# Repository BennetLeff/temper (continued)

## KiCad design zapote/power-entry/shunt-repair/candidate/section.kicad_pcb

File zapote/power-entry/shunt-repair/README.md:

# Shunt repair and electrical-model completion

Execution contract, 2026-09-16, starting at b7af4c912.

The approved work is shunt/copper thermal modeling, remaining current paths,
actual switching loops and startup/fault/loss-of-bias behavior. First resolve
an invalid model input: the authored WSL2726R0100FEA at 10 mΩ with two pads
is outside Vishay's published WSL2726 range and four-terminal package.
Source/native agreement did not detect this part-definition defect.

1. Retain exact manufacturer evidence and choose an available 10 mΩ shunt,
   preserving the controller's sense scaling. Bind MPN, resistance, package,
   land pattern and conditional power rating in Rust. Preserve the historical
   board as a failing regression; never rewrite historical source receipts.
2. Update authored source, compile with Atopile, refresh the saved working
   PCB/schematic and native receipts, and run construction/physical checks.
3. Model actual new shunt/copper geometry with explicit cooling and material
   uncertainty. Require energy balance, mesh convergence and sensitivities;
   a catalog wattage is not a temperature prediction or assembly qualification.
4. Resolve switching-loop and controller protection paths from source and
   manufacturer behavior. Keep missing external supervision and response-time
   bounds visible. Do not invent a safety deadline.
5. Run common harness and regression mutations; retain raw inputs/results and
   record remaining model or assembly limitations before committing/pushing.

Evidence belongs here and in a dated common-suite run. Historical GBU/GBJ
thermal results remain valid only for their original saved inputs. A changed
board is not allowed to inherit their acceptance by editing a hash.

No fabrication, purchase or powered measurement is part of this execution.

## Implemented repair

The working authoring source now uses GBJ2510-F and Stackpole
HCSM2818FT10L0 (10 mΩ, ±1%, two terminals). The historical GBU and GBJ
fixtures remain unchanged. Their unsupported WSL2726 shunt definition is now
an explicit `ERC.PFC.SHUNT_PART` failure, including in regression tests.

The replacement was compiled through Atopile, projected into native KiCad,
then applied to the routed GBJ candidate with its physical UUIDs preserved.
The land pattern uses two 3.5 × 5.3 mm rectangles, a 0.6 mm gap and a
7.15 × 4.95 mm body. The official KiCad Library Tools generator and parameters
are retained. Manufacturer documents, exact identities and source hashes are
in [sources/manifest.json](sources/manifest.json).

U12's left power trace is 5.3 mm wide and ends at (75.3, 132) mm, retaining
the sense-wire junction. A 6 mm trace ending there would short the new opposite
pad; shortening it first to 74.7 mm avoided that short but left a width-only
contact that the current graph could not resolve. The final edit repairs both
conditions. Its round cap stops at x = 77.95 mm; the opposite pad begins at
78.30 mm. Native DRC checks the resulting 0.35 mm clearance. The narrower trace
is subject to the same current screen as every other trace; no waiver was added.

Authoritative candidate: [candidate/section.kicad_pcb](candidate/section.kicad_pcb).
Use [units.json](units.json) to run the seven-unit suite with this working
candidate. The default maintained registry intentionally retains its historical
board; it does not silently acquire this candidate or its thermal evidence.

## What the thermal experiment establishes

[thermal-04/report.json](thermal-04/report.json) contains 15 actual Gmsh/Elmer
solves: five boundary/material/heat-split cases on three successively finer
meshes. Native front pads, local track rectangles and round ends are modeled
as separate copper domains. Independent Rust checks integrate mesh volumes,
check pad source volumes and cut areas, reject a bridged gap or internal clamp,
and require two connected domains with cooling boundaries. Both the Gmsh and
converted Elmer meshes are checked.

The heat source is 2.28528 W: 15 A RMS through 10 mΩ, with +1% resistance and
+75 ppm/K evaluated at 100 °C. It is a conditional input, not a temperature-
iterated worst-case bound. Heat balance, solver convergence and mesh convergence
are checked from raw output. Uniformly raising cut temperatures by 20 K raises
the result by 20 K; reducing copper conductivity from 350 to 250 W/(m·K)
scales the rise by 1.4, providing independent linear-equation checks.

| Case, finest mesh | Peak modeled local copper |
|---|---:|
| 80 °C cuts, equal terminal heat | 122.68 °C |
| 80 °C cuts, all heat into terminal 1 | 162.74 °C |
| 80 °C cuts, all heat into terminal 2 | 165.37 °C |
| 100 °C cuts, equal terminal heat | 142.68 °C |
| 80 °C cuts, weaker copper conductivity | 139.76 °C |

These are **not predictions of resistor body temperature or evidence that the
real board overheats**. The model omits body/solder conduction, vias, back copper,
FR4, convection and copper Joule heat. Parallel heat paths may cool the actual
assembly; other losses may heat it. The imposed cut temperatures need a board/
assembly cooling model. The 5 W catalog rating requires specified copper and
surface temperature conditions, which this model does not establish.
`THERMAL.PFC.SHUNT_ASSEMBLY` therefore remains INDETERMINATE.

Replay binds the exact saved board, source-bound 15 A waveform, geometry, decks,
backend/module digests, meshes, raw logs and measurements. Edited summaries,
changed decks even with updated checksums, missing heat materials, incorrect
boundaries, nonconverged solves and unbalanced heat are regression failures.
The first empty-region mesher attempt and subsequent historical runs are kept
as development evidence; they cannot be substituted for this final run.

## Controller and switching-loop coverage

The common runner executes the source-bound UCC28180 threshold cases. UVLO,
standby, high OVP/reset, open current sense, soft current limit and peak current
limit distinguish guaranteed threshold crossings from tolerance bands.
The ICOMP table/prose unit conflict remains INDETERMINATE. No guaranteed
shutdown propagation time or gate-voltage behavior at zero bias is invented.
Controller inhibition does not disconnect mains or discharge the DC bus.

Named boost-commutation, gate-drive and on-state input loops are checked against
source pin identities and native conductor paths. Bridge polarity is resolved
from its exact MPN. Returned edge IDs are connectivity witnesses, not extracted
high-frequency current paths. Loop geometry and parasitic inductance remain
explicit mandatory INDETERMINATE checks; a whole-net bounding box cannot satisfy
them.

## Remaining physical obligations

1. Resolve shunt body/terminal thermal parameters and actual board cooling,
   including vias and back copper; then evaluate resistor surface temperature
   and transient/pulse capability under the operating envelope.
2. Extract high-frequency return paths and parasitics for the named loops.
3. Supply the external bias, permit/precharge, disconnect and discharge contracts;
   validate their startup and fault timing with the power stage.
4. Complete inductor, switch, diode, capacitor and remaining pad/via loss/rating
   corners before calling the power-entry assembly qualified.

The new checks make these omissions visible. Numerical PASS, source agreement
and native DRC PASS are each narrower than hardware qualification.

## Final validation, 2026-09-16

[Final receipt](evidence/final-validation.json) binds the board and source hashes.
The [seven-unit run](../../validation/runs/shunt-20260916-final-02/summary.json)
has zero native ERC/DRC/unconnected/parity findings and zero Rust failures.
Every overall unit verdict remains INDETERMINATE because physical/integration
obligations are not waived. The workspace tests report 473 passed, zero failed,
one ignored. Clippy reports only the 15 previously present warnings; import
boundaries and generated-artifact consistency checks pass.

The bridge evidence was regenerated from this exact candidate: 96 local solves
under [bridge-thermal-02](bridge-thermal-02/assessment.json), with nominal mesh
deltas 0.04383/0.02454 K and wider-domain delta 0.01685 K. No historical bridge
result was made current by changing its input hash. Required raw meshes, scalar
measurements, decks, logs and tool receipts are retained; gzip archives preserve
their original-byte hashes. Optional nodal restart fields are retained locally
at the location and digests recorded in `bridge-thermal-02/field-archive.json`;
they are not inputs to the acceptance replay.

`shunt-20260916-final` is a rejected attempt: archiving those optional restart
fields overlapped its input read, and the integrity guard refused the run.
`shunt-20260916-final-02` is the completed immutable-input rerun. Earlier failed
geometry, copper and model attempts are retained with their actual outcomes.

[Code-review receipt](../../../docs/reviews/shunt-20260916/run-20260916-shunt/review.json)
reports no actionable findings. Its coverage limitations are retained. No
hardware was powered, no purchase was placed and no fabrication order was made.

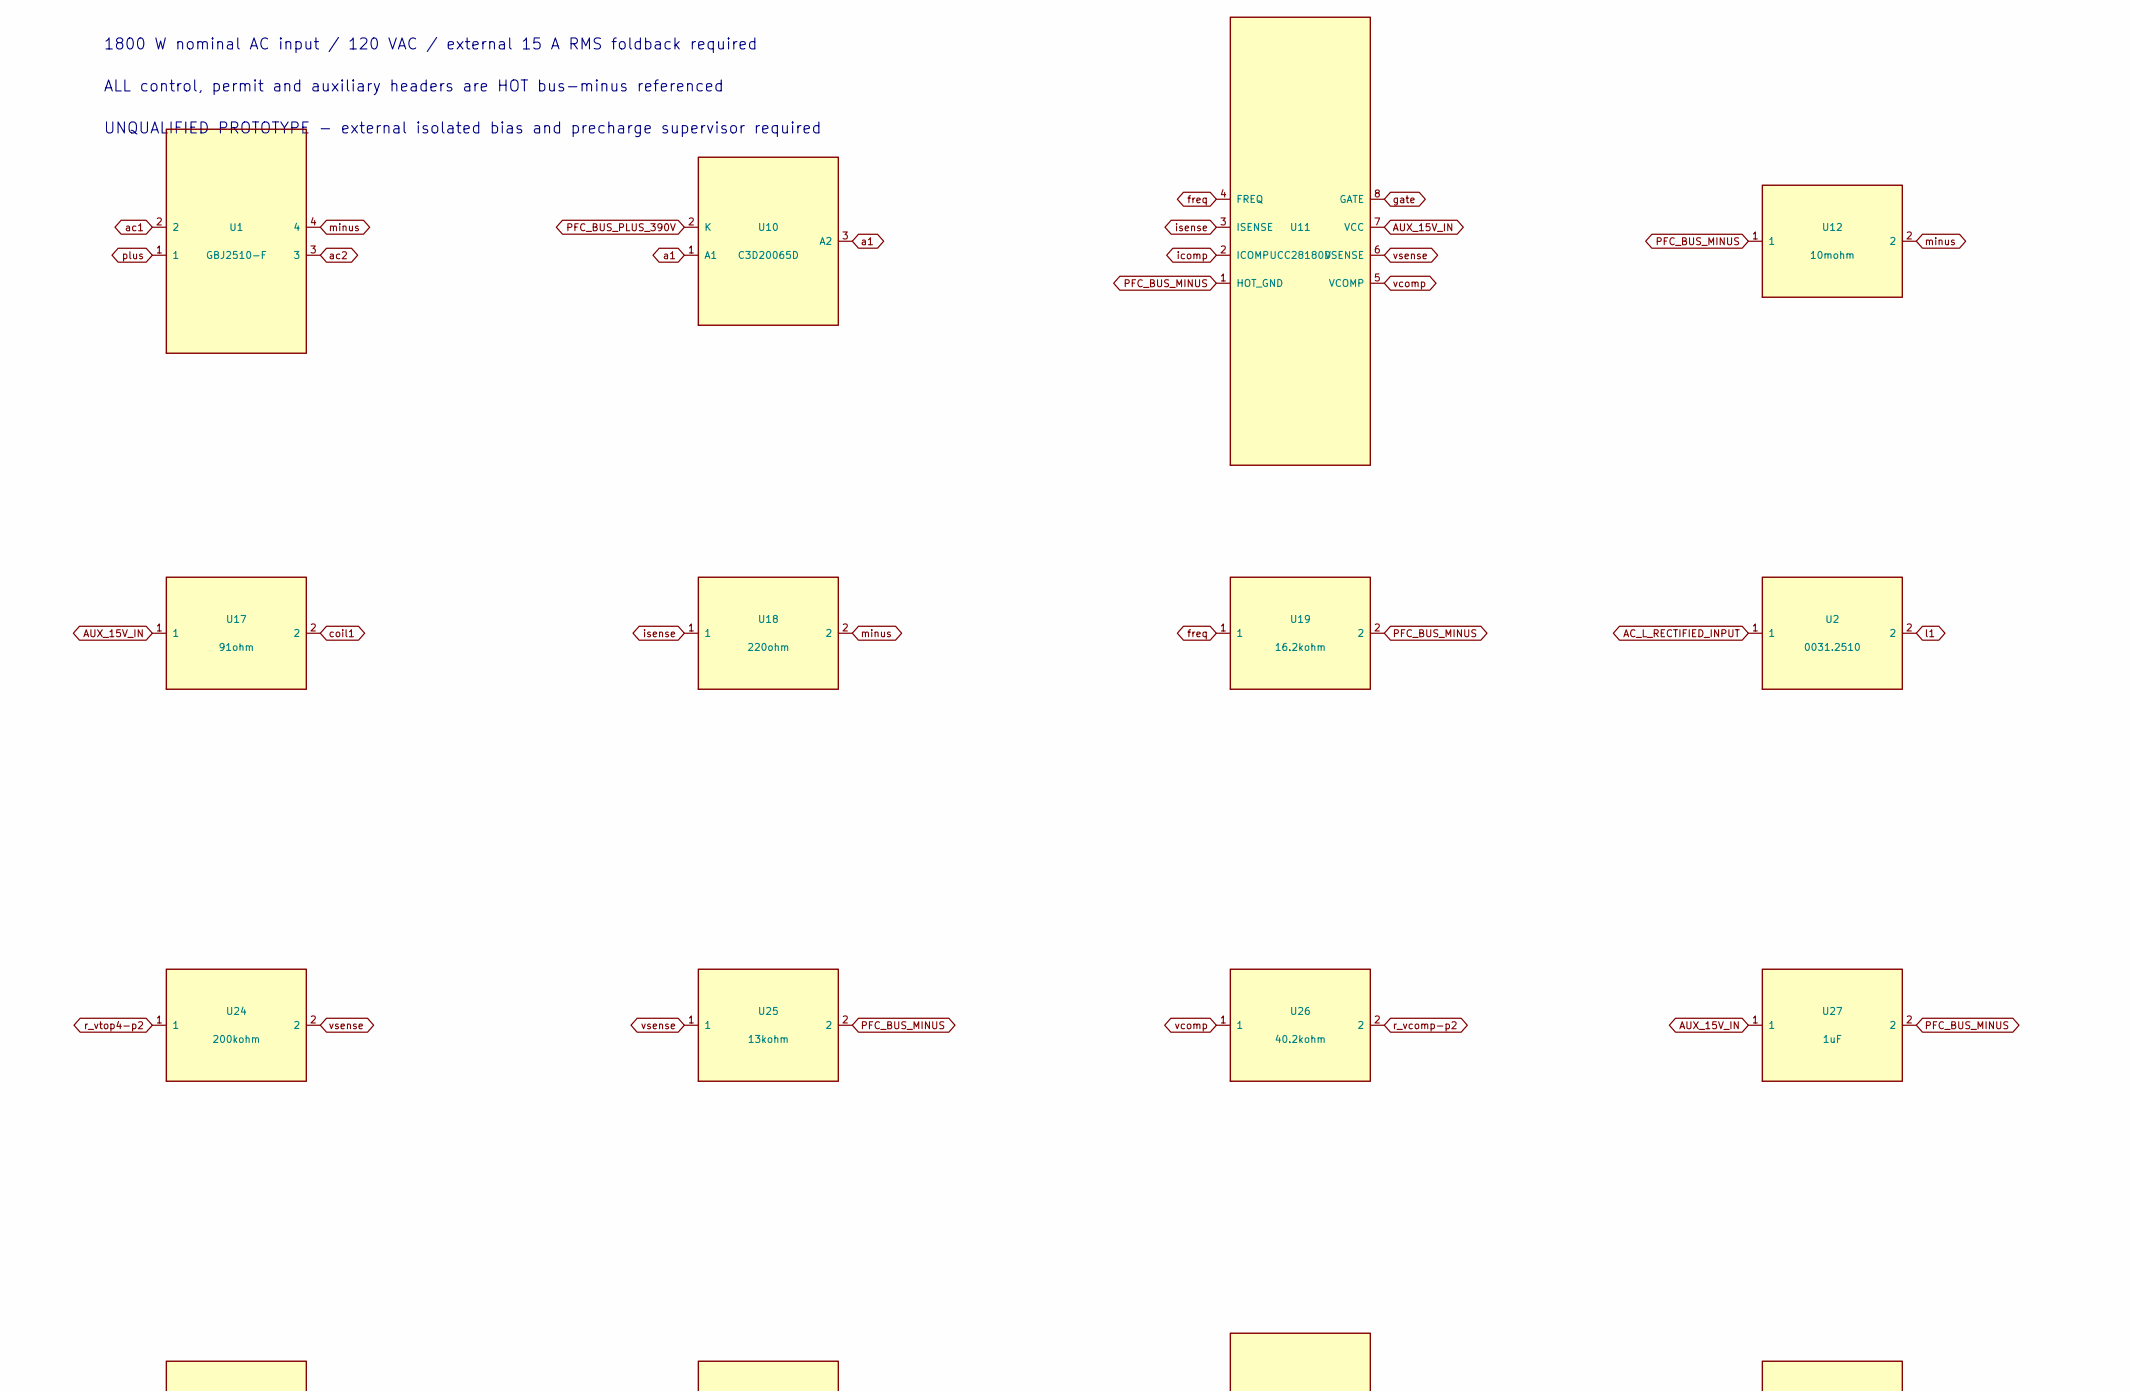
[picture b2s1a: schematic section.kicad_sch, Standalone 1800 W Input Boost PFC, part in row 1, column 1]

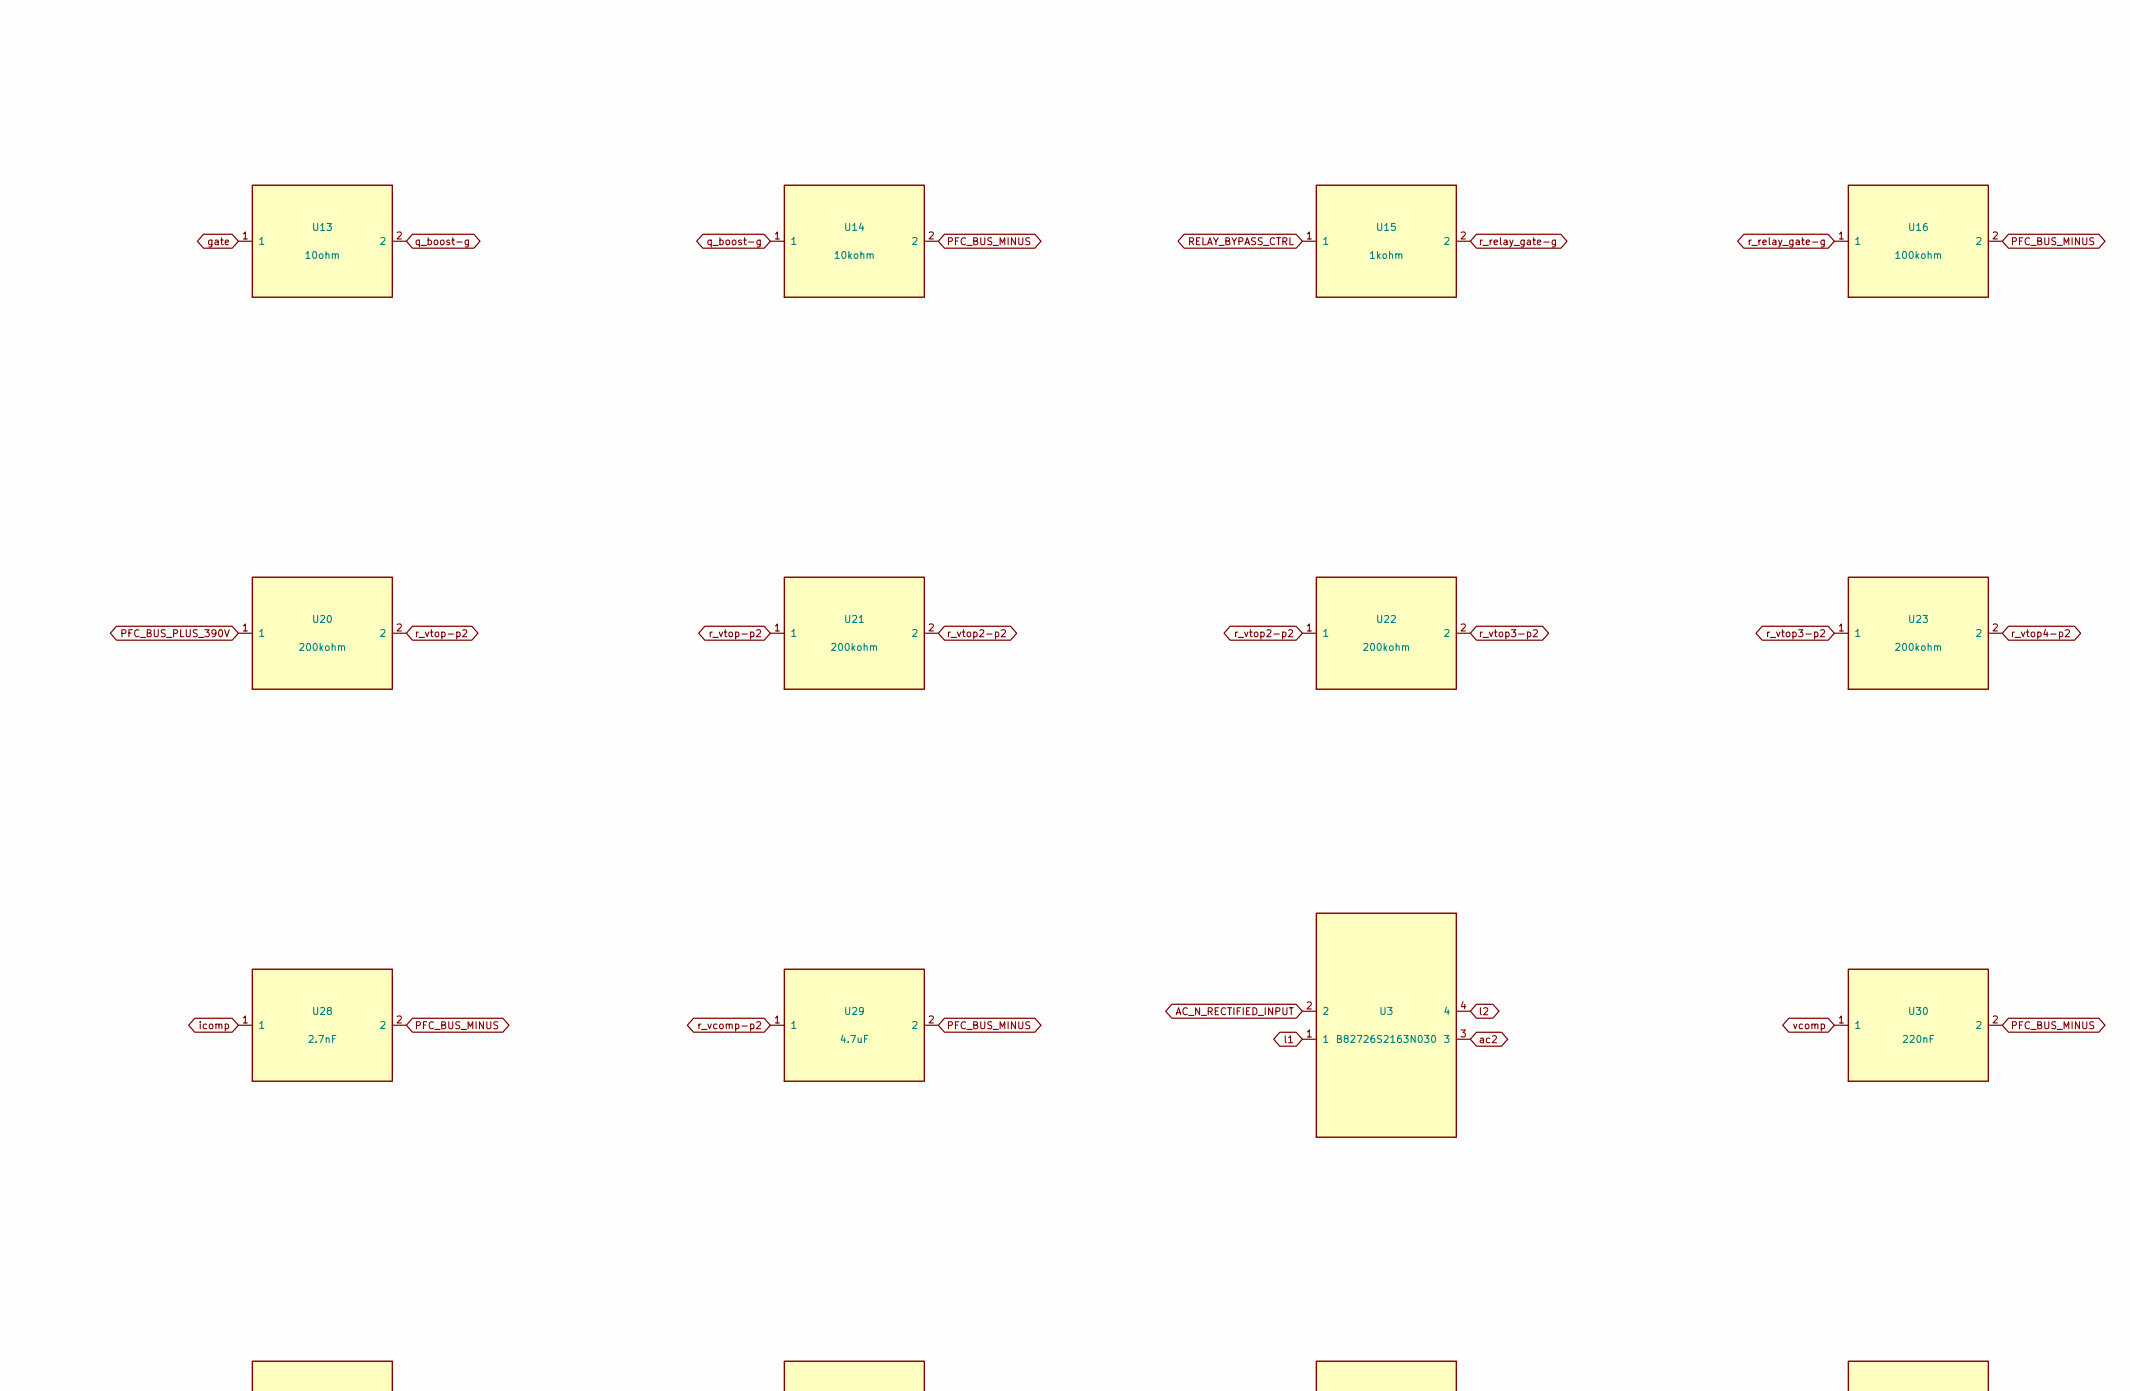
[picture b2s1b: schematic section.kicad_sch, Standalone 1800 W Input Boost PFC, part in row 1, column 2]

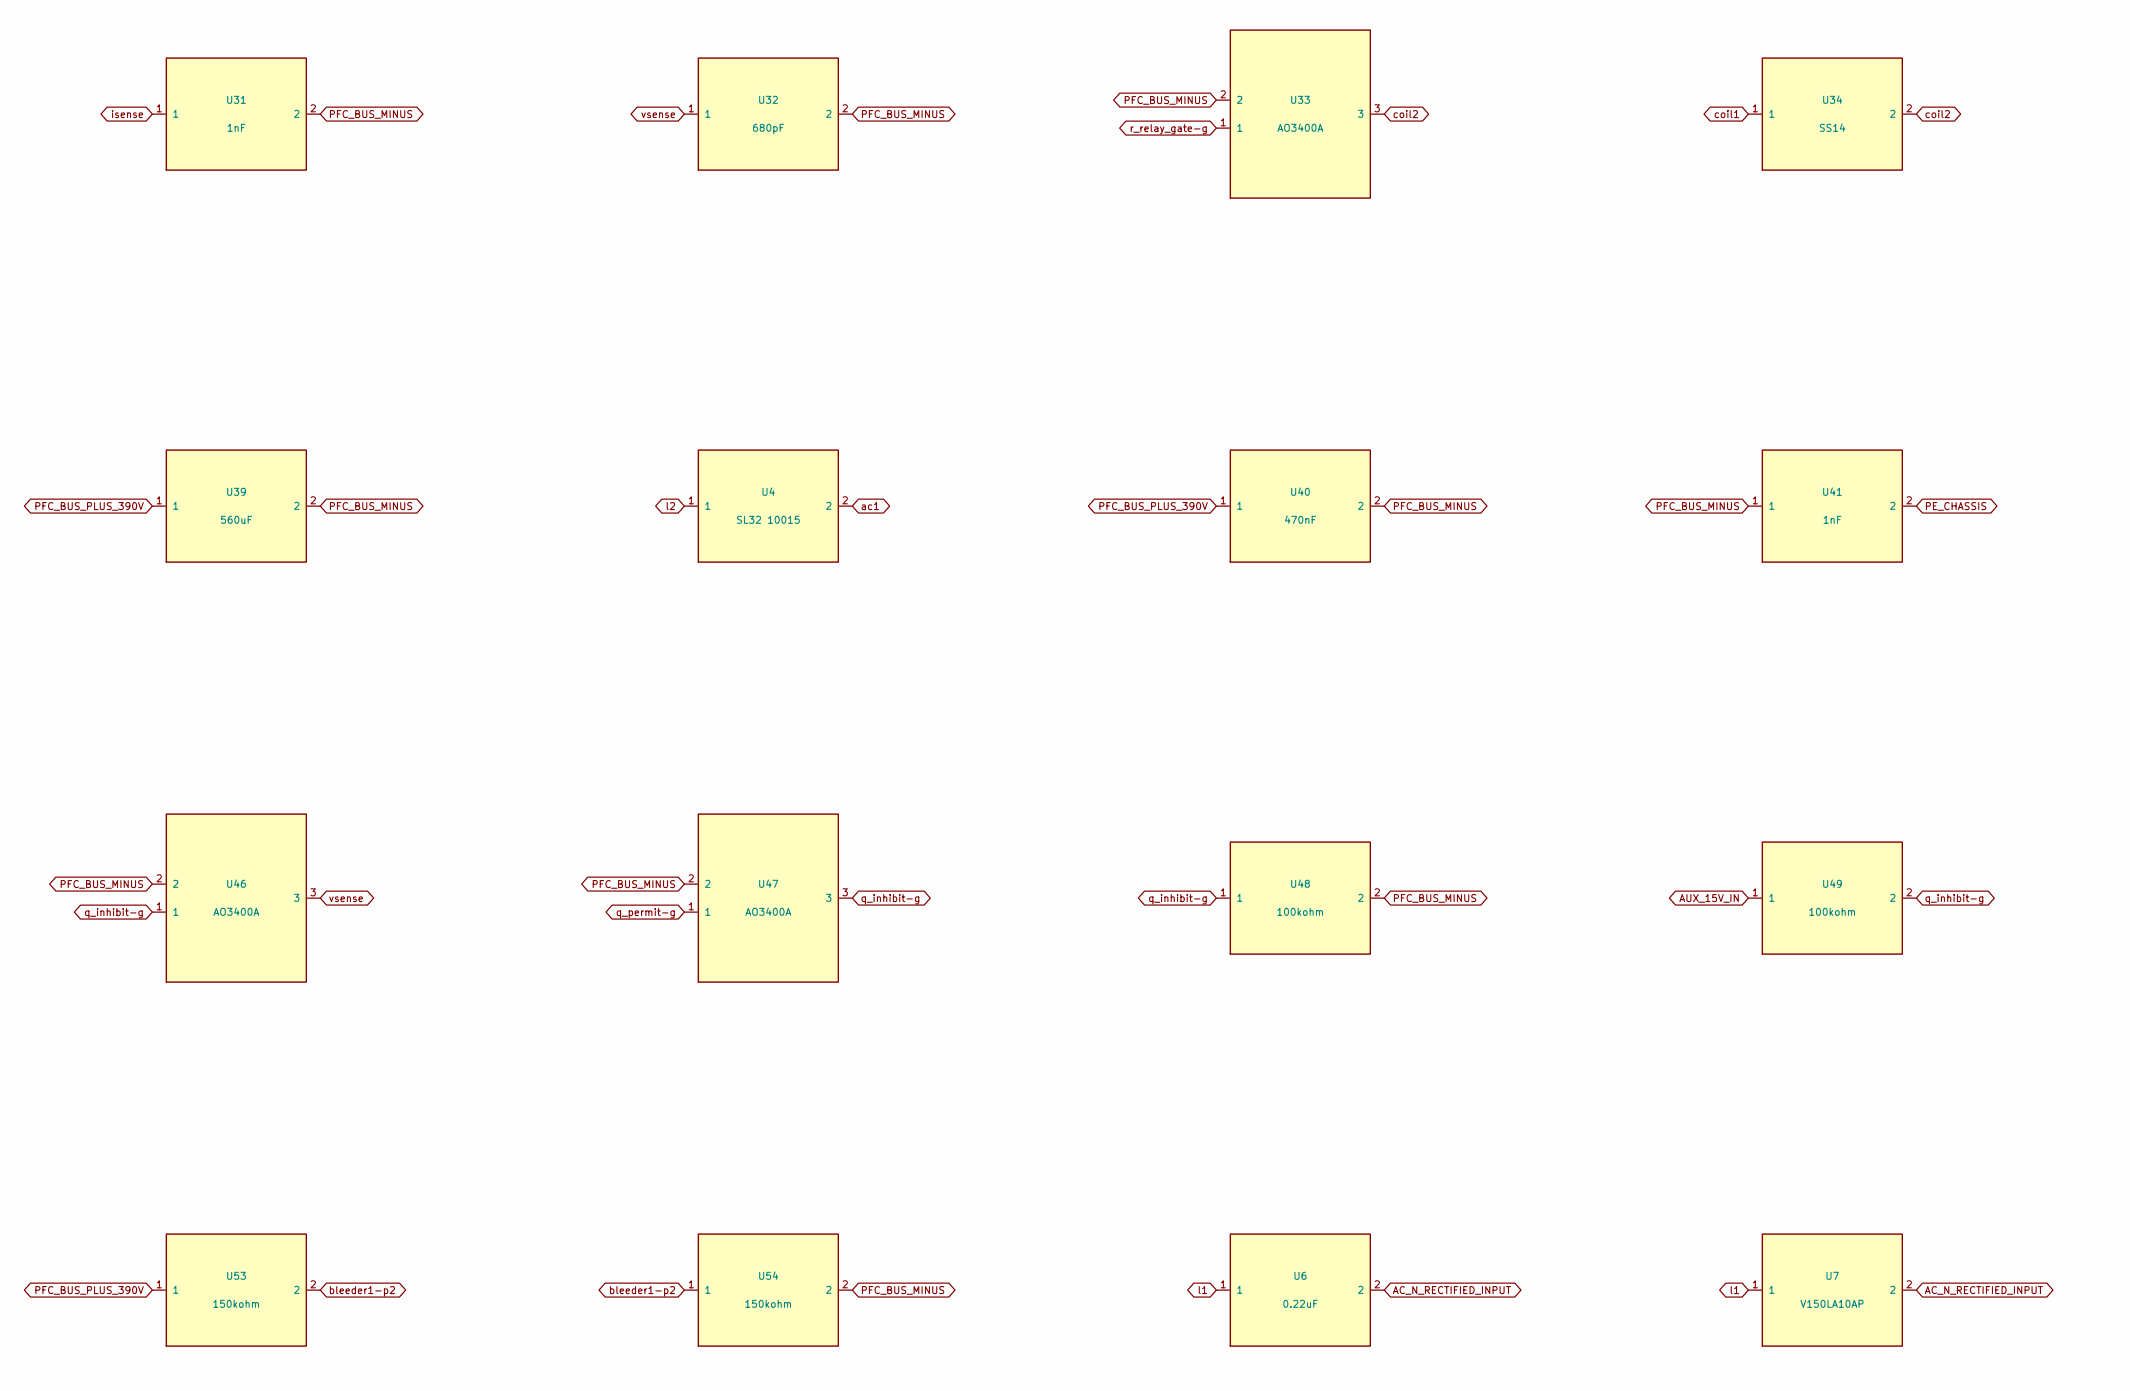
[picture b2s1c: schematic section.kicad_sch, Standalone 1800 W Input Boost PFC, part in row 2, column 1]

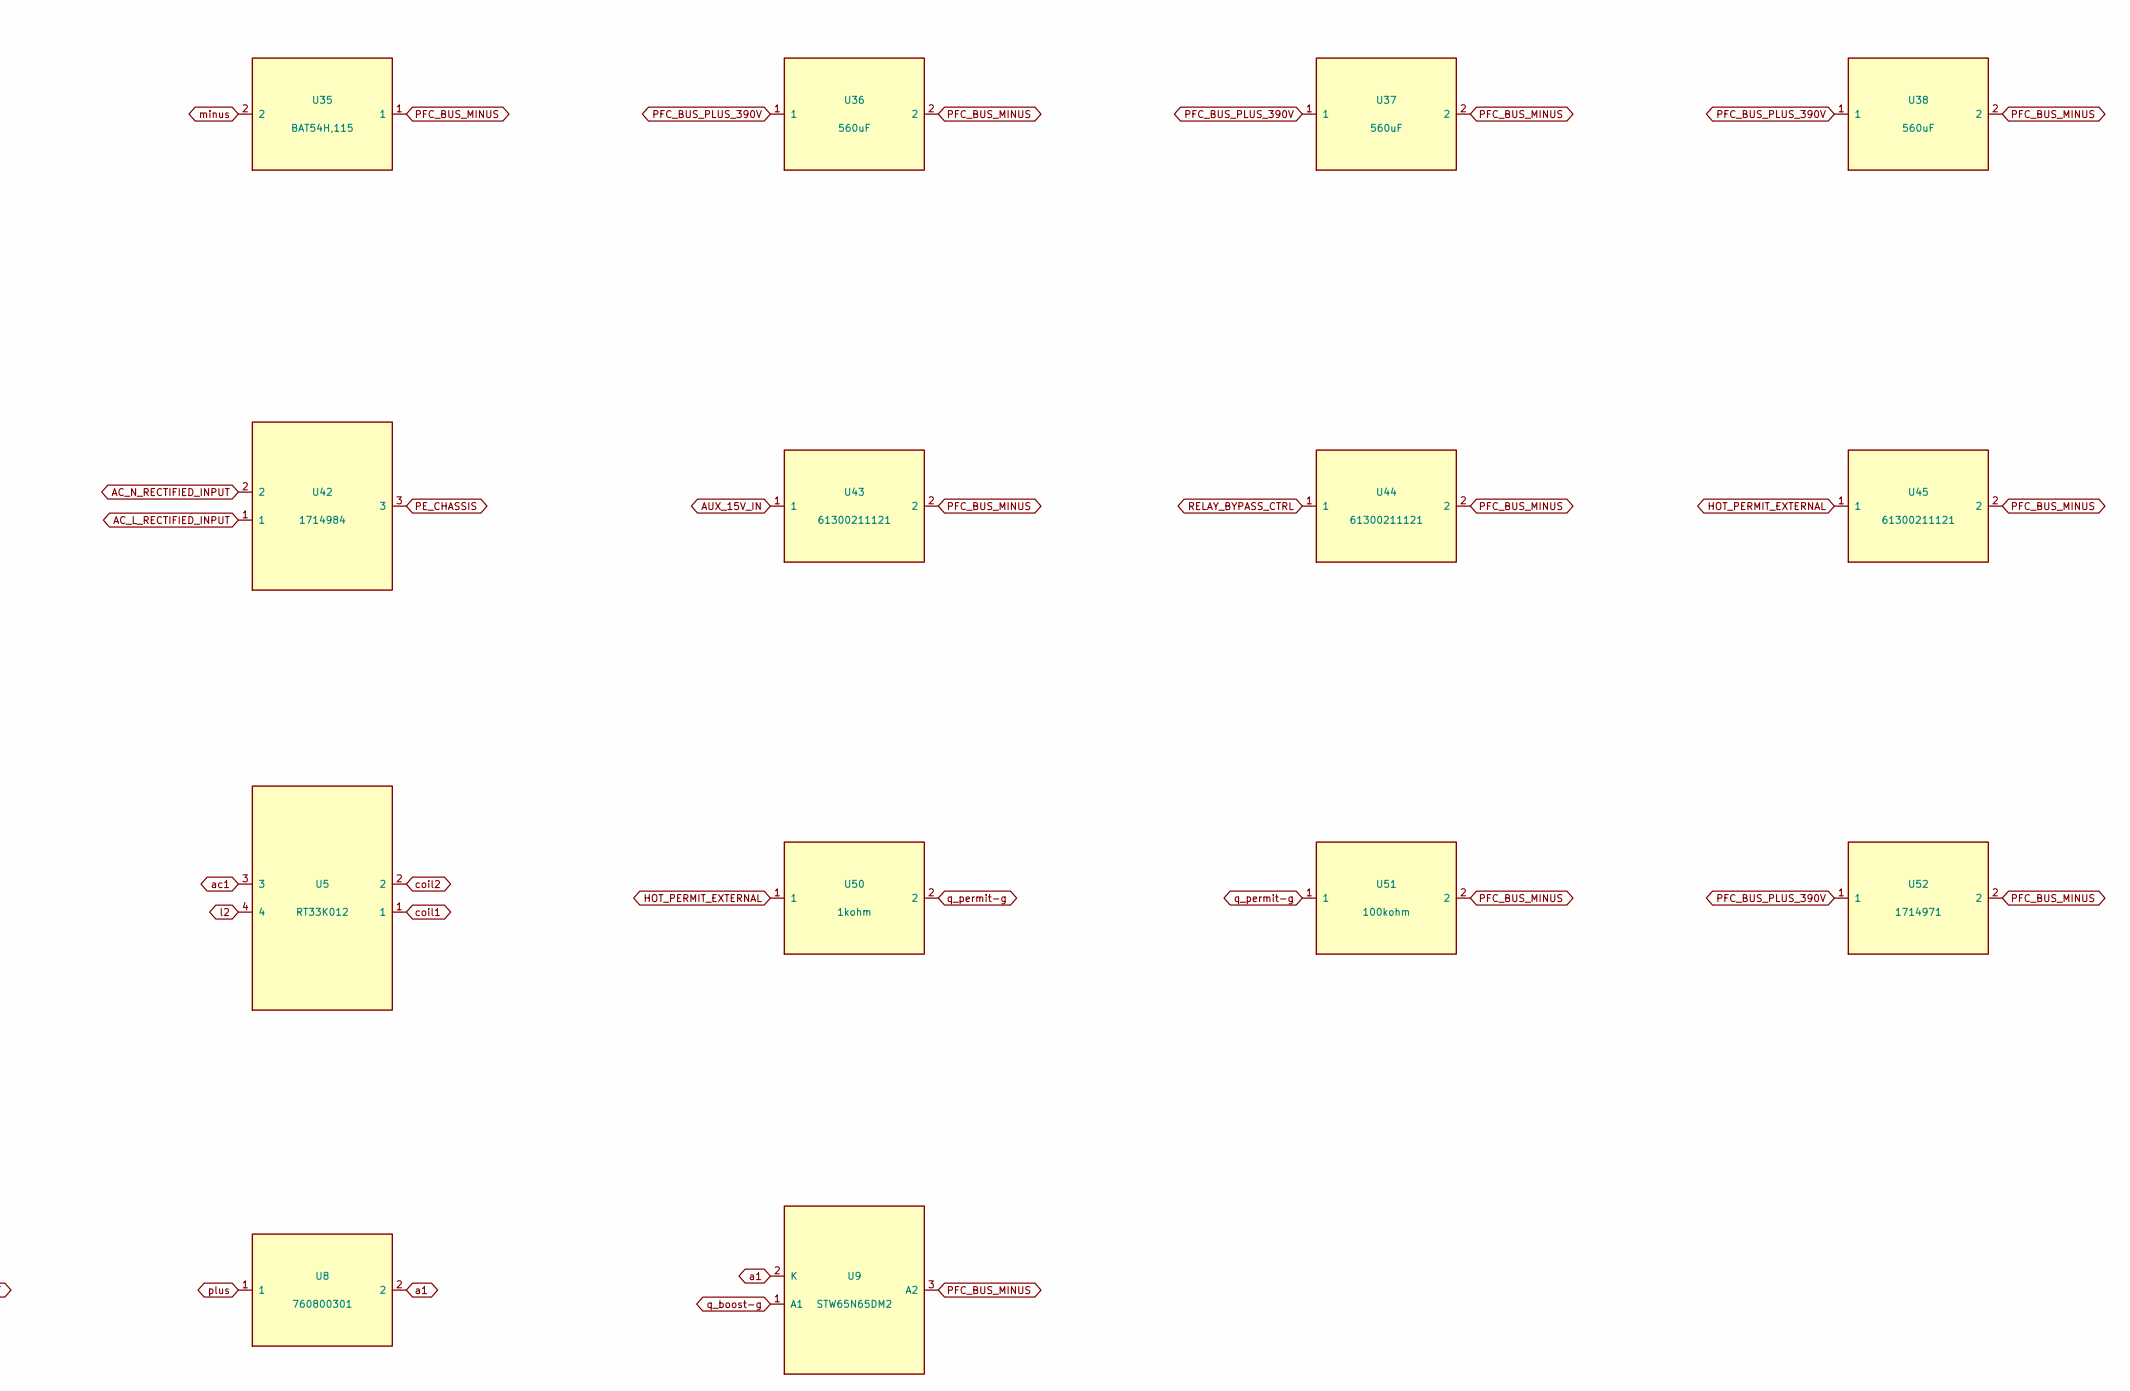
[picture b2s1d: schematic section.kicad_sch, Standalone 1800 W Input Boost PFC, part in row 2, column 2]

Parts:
U1: GBJ2510-F; Diode_Bridge_GBJ2510
U2: 0031.2510; Fuseholder_Cylinder-5x20mm_Schurter_FUP_0031.2510_Horizonta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
U3: B82726S2163N030; CMC_B82726S
U4: SL32 10015; SL32_10015
U5: RT33K012; Relay_SPST_Schrack-RT33K012
U6: 0.22uF; C_Rect_L18.0mm_W7.0mm_P15.00mm_FKS3_FKP3
U7: V150LA10AP; RV_Disc_D15.5mm_W5.2mm_P7.5mm
U8: 760800301; L_Wurth_WE-TORPFC-T75
U9: STW65N65DM2; TO-247-3_Vertical
U10: C3D20065D; TO-247-3_Vertical
U11: UCC28180D; SOIC-8_3.9x4.9mm_P1.27mm
U12: 10mohm; HCSM2818FT10L0
U13: 10ohm; R_1206_3216Metric
U14: 10kohm; R_1206_3216Metric
U15, U50: 1kohm; R_1206_3216Metric
U16, U48, U49, U51: 100kohm; R_1206_3216Metric
U17: 91ohm; R_2512_6332Metric
U18: 220ohm; R_1206_3216Metric
U19: 16.2kohm; R_1206_3216Metric
U20, U21, U22, U23, U24: 200kohm; R_2512_6332Metric
U25: 13kohm; R_1206_3216Metric
U26: 40.2kohm; R_1206_3216Metric
U27: 1uF; C_0805_2012Metric
U28: 2.7nF; C_0805_2012Metric
U29: 4.7uF; C_1210_3225Metric
U30: 220nF; C_0805_2012Metric
U31: 1nF; C_0805_2012Metric
U32: 680pF; C_0805_2012Metric
U33, U46, U47: AO3400A; SOT-23
U34: SS14; D_SMA
U35: BAT54H,115; D_SOD-123F
U36, U37, U38, U39: 560uF; CP_Radial_D35.0mm_P10.00mm_SnapIn
U40: 470nF; B32672P6474K000
U41: 1nF; C_Disc_Vishay_VY1102M31Y5UQ63V0
U42: 1714984; Phoenix_1714984
U43, U44, U45: 61300211121; PinHeader_1x02_P2.54mm_Vertical
U52: 1714971; Phoenix_1714971
U53, U54: 150kohm; R_2512_6332Metric

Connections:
AC_L_RECTIFIED_INPUT: U2.1, U42.1
AC_N_RECTIFIED_INPUT: U3.2, U6.2, U7.2, U42.2
AUX_15V_IN: U11.7 (VCC), U17.1, U27.1, U43.1, U49.1
HOT_PERMIT_EXTERNAL: U45.1, U50.1
PE_CHASSIS: U41.2, U42.3
PFC_BUS_MINUS: U9.3 (A2), U11.1 (HOT_GND), U12.1, U14.2, U16.2, U19.2, U25.2, U27.2, U28.2, U29.2, U30.2, U31.2, U32.2, U33.2, U35.1, U36.2, U37.2, U38.2, U39.2, U40.2, U41.1, U43.2, U44.2, U45.2, U46.2, U47.2, U48.2, U51.2, U52.2, U54.2
PFC_BUS_PLUS_390V: U10.2 (K), U20.1, U36.1, U37.1, U38.1, U39.1, U40.1, U52.1, U53.1
RELAY_BYPASS_CTRL: U15.1, U44.1
a1: U8.2, U9.2 (K), U10.1 (A1), U10.3 (A2)
ac1: U1.2, U4.2, U5.3
ac2: U1.3, U3.3
bleeder1-p2: U53.2, U54.1
coil1: U5.1, U17.2, U34.1
coil2: U5.2, U33.3, U34.2
freq: U11.4 (FREQ), U19.1
gate: U11.8 (GATE), U13.1
icomp: U11.2 (ICOMP), U28.1
isense: U11.3 (ISENSE), U18.1, U31.1
l1: U2.2, U3.1, U6.1, U7.1
l2: U3.4, U4.1, U5.4
minus: U1.4, U12.2, U18.2, U35.2
plus: U1.1, U8.1
q_boost-g: U9.1 (A1), U13.2, U14.1
q_inhibit-g: U46.1, U47.3, U48.1, U49.2
q_permit-g: U47.1, U50.2, U51.1
r_relay_gate-g: U15.2, U16.1, U33.1
r_vcomp-p2: U26.2, U29.1
r_vtop2-p2: U21.2, U22.1
r_vtop3-p2: U22.2, U23.1
r_vtop4-p2: U23.2, U24.1
r_vtop-p2: U20.2, U21.1
vcomp: U11.5 (VCOMP), U26.1, U30.1
vsense: U11.6 (VSENSE), U24.2, U25.1, U32.1, U46.3

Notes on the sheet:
1800 W nominal AC input / 120 VAC / external 15 A RMS foldback required
ALL control, permit and auxiliary headers are HOT bus-minus referenced
UNQUALIFIED PROTOTYPE - external isolated bias and precharge supervisor required

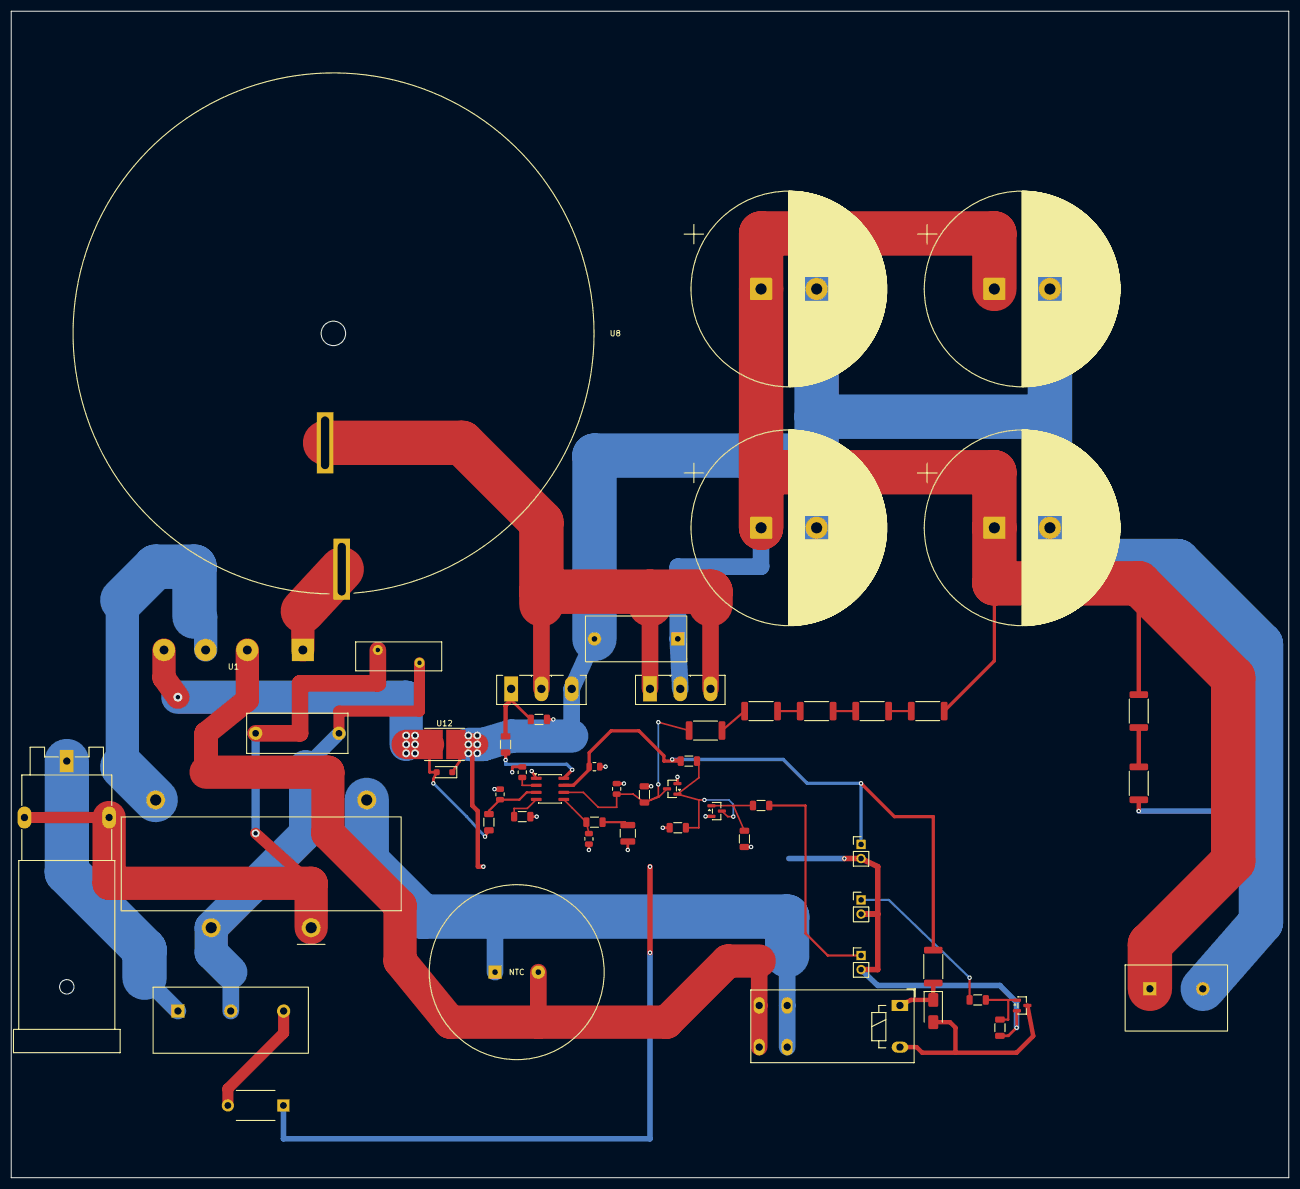
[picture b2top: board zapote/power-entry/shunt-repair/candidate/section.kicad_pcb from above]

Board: 2 copper layers, 230.0 x 210.0 mm, 54 parts (0 on the bottom side), 33 nets.
